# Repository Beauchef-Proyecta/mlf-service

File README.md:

# mlf-service
Send frames from a robot webcam to a browser through webrtc. Other webrtc connections are available.

## Running 

First install the requirements 

    $ pip install -r requirements.txt

When you start the example, it will create an HTTP server which you can connect to from your browser or other application:

    $ python webcam.py

### From browser

You can then browse to the following page with your browser:

http://{nombre-pony}.local:8080

Once you click Start the server will send video from its webcam to the browser.

Warning

Due to the timing of when Firefox starts responding to mDNS requests and the current lack of ICE trickle support in aiortc, this example may not work with Firefox.

### From other aplication

You can start a webrtc connection sending your RTCSessionDescription to the following page:

    http://{nombre-pony}.local:8080/offer

And saving the RTCSessionDescription that it will respond.

For an example see https://github.com/Beauchef-Proyecta/mlf-api

## Proyect Description
webcam.py: Run the server for the signaling and streaming.

index.html: Webpage that show the video stream.

client.js: Manage the WebRTC connection in the client.

## Agregar offsets
ejecutar el siguiente comando

    $ echo 'export OFFSETS = "<offset1>,<offset2>,<offset3>,<offset4>"' >> ~/.bashrc
Para editar o eliminarlas

    $ nano ~/.bashrc
y al final del archivo hay que editarlas.

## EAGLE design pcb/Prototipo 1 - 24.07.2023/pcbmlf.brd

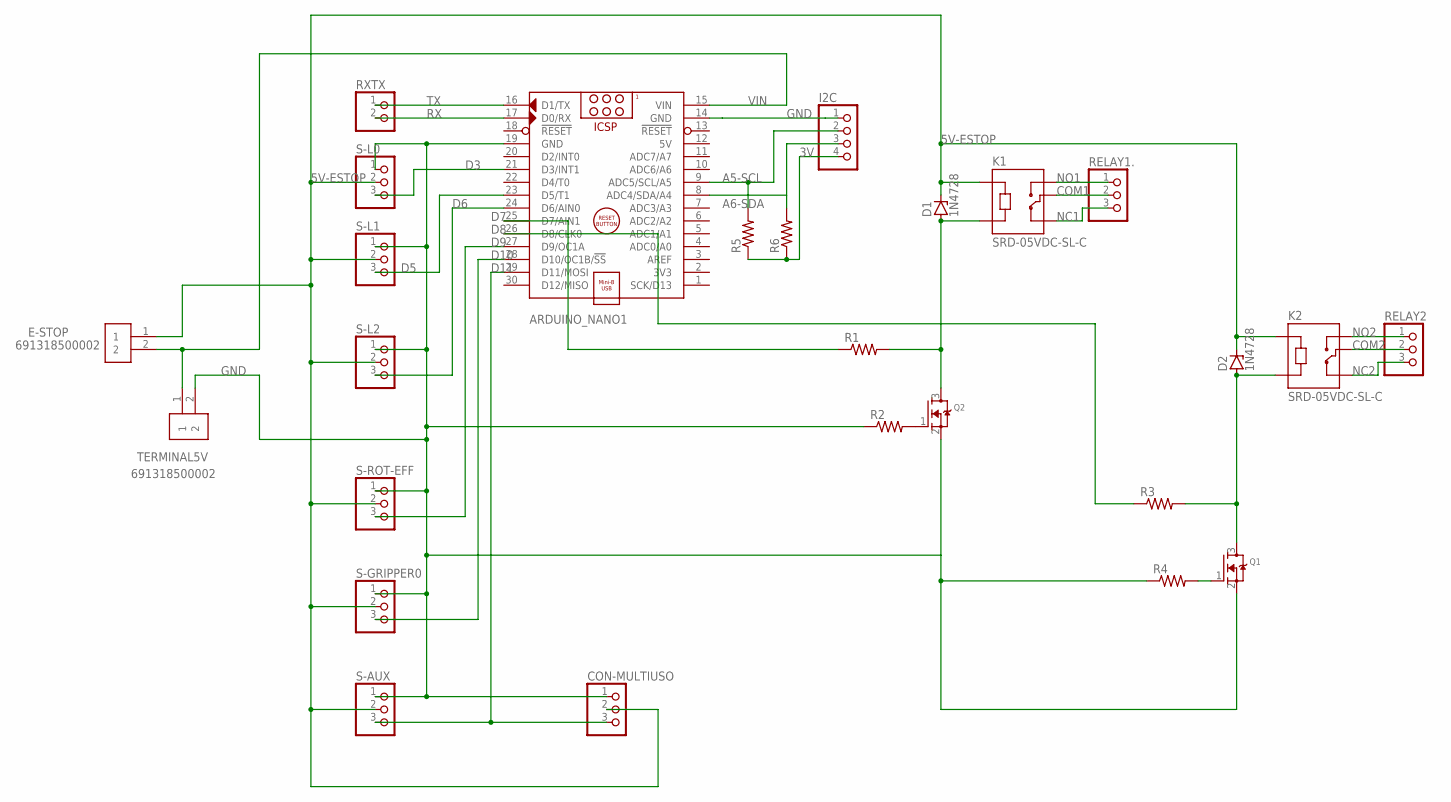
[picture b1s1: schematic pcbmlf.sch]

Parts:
ARDUINO_NANO1: ARDUINO_NANO
CON-MULTIUSO: PINHD-1X3; 1X03
D1, D2: 1N4728; DO41Z10
E-STOP: 691318500002; TERMINALBLOCK_PLUGGABLE-2-5.08MM
I2C: PINHD-1X4; 1X04
K1, K2: SRD-05VDC-SL-C; RELAY_SRD-05VDC-SL-C
Q1, Q2: MOSFET-NWAVE; SOT23-W
R1, R2, R3, R4, R5, R6: R-US_R0805; R0805
RELAY1., RELAY2: PINHD-1X3; 1X03
RXTX: PINHD-1X2; 1X02
S-AUX: PINHD-1X3; 1X03
S-GRIPPER0: PINHD-1X3; 1X03
S-L0, S-L1, S-L2: PINHD-1X3; 1X03
S-ROT-EFF: PINHD-1X3; 1X03
TERMINAL5V: 691318500002; TERMINALBLOCK_PLUGGABLE-2-5.08MM

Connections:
3V: I2C.4, R5.1, R6.1
5V: ARDUINO_NANO1.12 (5V)
5V-ESTOP: CON-MULTIUSO.2, D1.C, D2.C, E-STOP.1, K1.A1, K2.A1, S-AUX.2, S-GRIPPER0.2, S-L0.2, S-L1.2, S-L2.2, S-ROT-EFF.2
A5-SCL: ARDUINO_NANO1.9 (ADC5/SCL/A5), I2C.2, R5.2
A6-SDA: ARDUINO_NANO1.8 (ADC4/SDA/A4), I2C.3, R6.2
COM1: K1.COM, RELAY1..2
COM2: K2.COM, RELAY2.2
D3: ARDUINO_NANO1.21 (D3/INT1), S-L0.3
D5: ARDUINO_NANO1.23 (D5/T1), S-L1.3
D6: ARDUINO_NANO1.24 (D6/AIN0), S-L2.3
D7: ARDUINO_NANO1.25 (D7/AIN1), R1.1
D8: ARDUINO_NANO1.26 (D8/CLK0), R3.1
D9: ARDUINO_NANO1.27 (D9/OC1A), S-ROT-EFF.3
D10: ARDUINO_NANO1.28 (D10/OC1B/!SS), S-GRIPPER0.3
D11: ARDUINO_NANO1.29 (D11/MOSI), CON-MULTIUSO.3, S-AUX.3
GND: ARDUINO_NANO1.14 (GND), ARDUINO_NANO1.19 (GND), CON-MULTIUSO.1, I2C.1, Q1.2 (S), Q2.2 (S), R2.1, R4.1, S-AUX.1, S-GRIPPER0.1, S-L0.1, S-L1.1, S-L2.1, S-ROT-EFF.1, TERMINAL5V.2
unnamed: Q2.1 (G), R2.2
unnamed: Q1.1 (G), R4.2
unnamed: D1.A, K1.A2, Q2.3 (D), R1.2
unnamed: D2.A, K2.A2, Q1.3 (D), R3.2
NC1: K1.NC, RELAY1..3
NC2: K2.NC, RELAY2.3
NO1: K1.NO, RELAY1..1
NO2: K2.NO, RELAY2.1
RX: ARDUINO_NANO1.17 (D0/RX), RXTX.2
TX: ARDUINO_NANO1.16 (D1/TX), RXTX.1
VIN: ARDUINO_NANO1.15 (VIN), E-STOP.2, TERMINAL5V.1

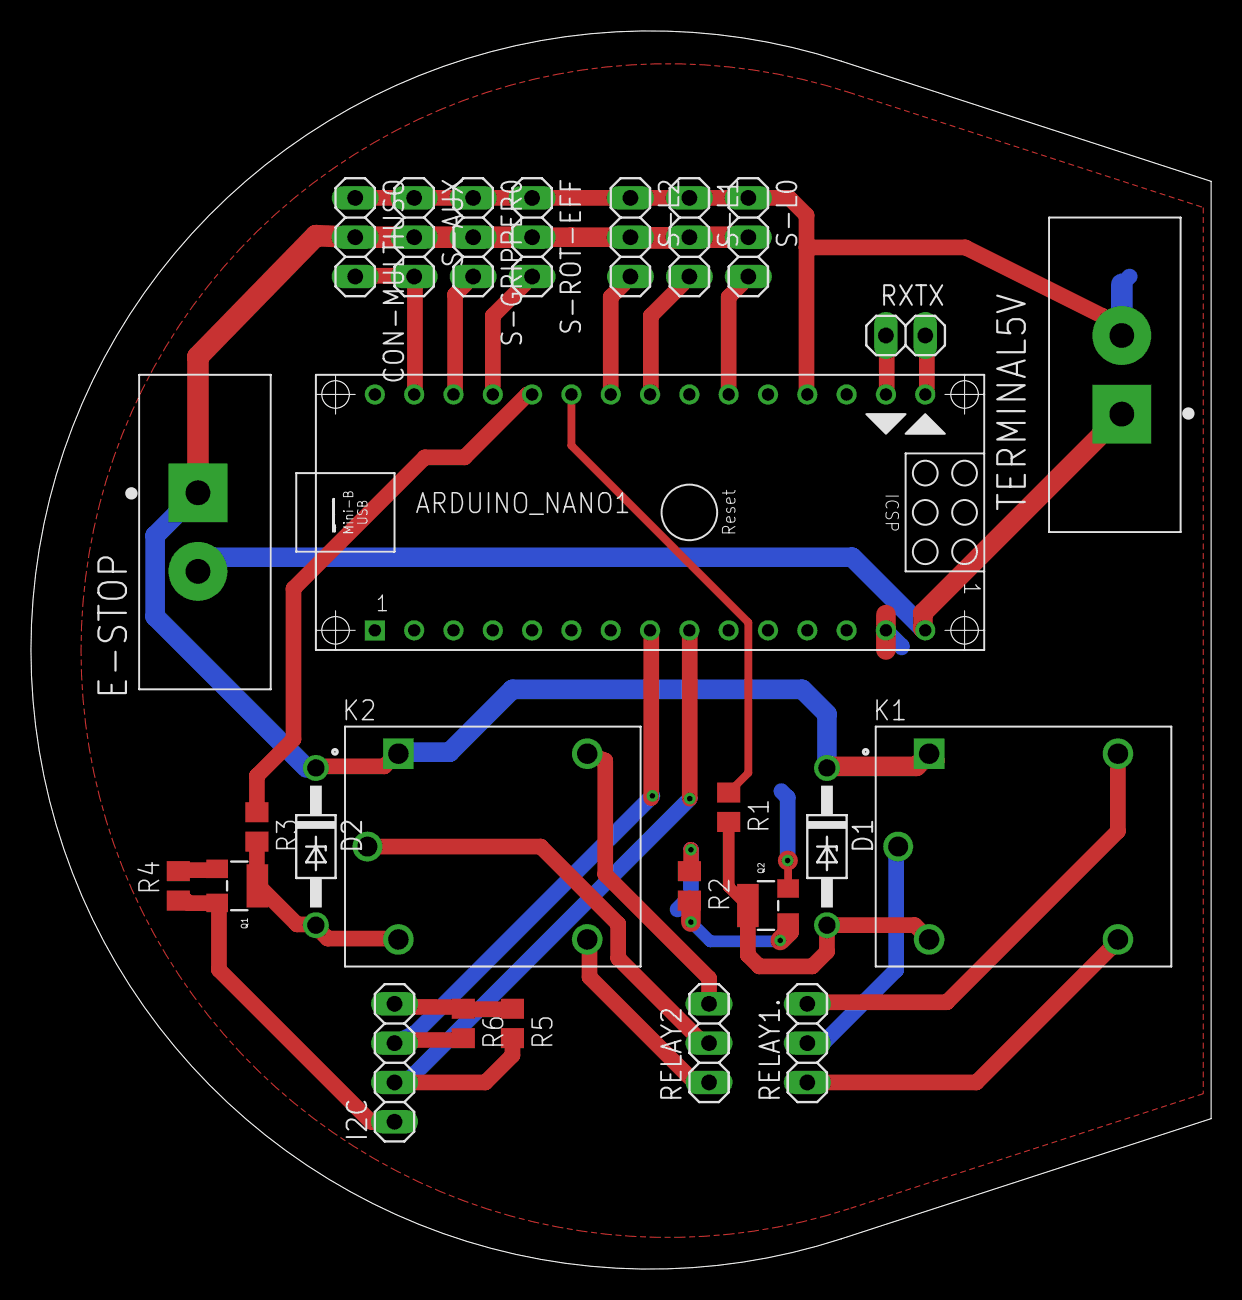
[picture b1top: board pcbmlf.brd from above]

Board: 2 copper layers, 76.2 x 80.0 mm, 26 parts (0 on the bottom side), 26 nets.

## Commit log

2023-04-14 added test files
2023-04-21 core and server
2023-04-21 first test
2023-04-28 update requirements
2023-04-28 README updated
2023-04-28 add: basic server
2023-04-28 add aiohttp to requirements
2023-04-28 change server ip and port
2023-05-05 add webcam script
2023-05-12 clean code
2023-05-12 Fix error when more than user connect
2023-05-19 docuemntation: Update README.md
2023-05-20 chore: add basic Dockerfile and docker-compose.yml
2023-05-26 feat: Add move server
2023-05-26 Add gitignore
2023-05-31 fix: Delete unused object
2023-06-09 add arduino firmware
2023-06-09 add gripper control
2023-06-16 fix bug
2023-06-16 add extra servo and relays
2023-06-16 add relays and extra servo
2023-06-16 add reelay and extra servo to server
2023-07-07 add arduino-correa
2023-07-24 prototipo 1 pcb agregado
2023-11-20 add joy.py and model of the robot
2023-11-22 add joy with an xbox controller
2023-11-22 add joy/sisifo and store path
2024-03-12 MG: update mk2_serial
2024-03-12 MG: hotfix joy
2024-03-22 MG: update dof on server
2024-03-22 MG: add start screen
2024-03-22 MG: ahora si
2024-04-12 add stop_server for automatic server stopping
2024-05-10 feat(arduino): Add get weight function
2024-05-10 Fix(arduino): Missing semicolon
2024-05-10 Fix(arduino): conversion from double to byte array
2024-05-10 feat(serial): Add recv method to client
2024-05-10 feat(client): Add get weight method
2024-05-10 feat(server): Add get weight url
2024-05-10 fix(serial): Add missing arg
2024-05-19 Fix(arduino): Update char to Unsigned char to access cmd array
2024-05-19 fix(arduino): Update cell clock and dout
2024-05-19 Fix(server): Update data read from arduino
2024-05-27 sonar working
2024-06-07 MG: distance workin
2024-06-07 MG: solve a bug where 2 bits were read when sending joint cmd (it should be 4 since we send 2 ints)
2024-06-07 MG: change debug mode to false
2024-06-28 MG: working AHORA SI
2024-07-01 feat: add offset
2024-07-01 Update env var name
2024-07-01 feat: add offsets str in connect
2024-07-01 Add readme to edit offsets
2024-10-11 MG: first commit, tof sensor sending data via serial comm
2024-10-11 MG: working tof request with another arduino
2024-10-11 MG: uncomment other routes
2024-10-11 MG: working pesa
2024-10-11 MG: fix return value
2024-10-18 MG: update pesa firmware
2024-11-08 MG: update arduino firmware
2025-11-08 Feat: Add Protocol to safely recv data
2025-11-08 Update readme.md
    Library for HX711
2025-11-10 MG: fix set_relay_status and add capture()
